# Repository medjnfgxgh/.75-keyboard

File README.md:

# .75-keyboard
An 83 key mechanical keyboard with a rotary encoder for volume and brightness. This was designed to be similar to a 75% keyboard.

### Why?
I was complaining to my friend about how terrible the keyboards in the computer labs at school are, and he suggested I bring my own. One problem, I don't have a spare keyboard. "Just make one", he said, "How hard could it be?". This was very clearly a joke but it did give me an idea for my next project, why not make my very own mechanical keyboard. It would test my CAD and PCB design skills, as well as my soldering, 3d printing and programming knowledge. After a little bit of research, I landed on my design with 83 keys and a rotary encoder.

## The design

## Schematic

## PCB

## Case

# BOM
|           Name           | QTY | Cost | Link |
|--------------------------|-----|------|------|
|Rasberry Pi Pico welded C |  1  |$2.63 |[buy](https://www.aliexpress.com/item/1005005617180169.html)|
|Cherry MX switches        |  9  |$2.33 |[buy](https://www.aliexpress.com/item/1005004341695529.html)|
|Stabilisers               |  1  |$6.82 |[buy](https://www.aliexpress.com/item/1005007041109896.html)|
|Key Caps                  |  1  |$21.62|[buy](https://www.aliexpress.com/item/1005007360831985.html)|
|diodes                    |  1  |$4.48 |[buy](https://www.aliexpress.com/item/1005008994213870.html)|
|EC11                      |  1  |$2.27 |[buy](https://www.aliexpress.com/item/1005007644083514.html)|
|Brass inserts             |  1  |$4.56 |[buy](https://www.aliexpress.com/item/1005006071488810.html)|
|Screws                    |  1  |$6.38 |[buy](https://www.aliexpress.com/item/1005006674812661.html)|
|Female Headers            |  1  |$3.34 |[buy](https://www.aliexpress.com/item/4001198421663.html)|
|subtotal                  |  1  |$73.07|
|Discounts                 |  1  |$-11.5|
|shipping                  |  1  |$7.39
|--------------------------|-----|------|-----|
|AliExpress total          |  1  |$68.96|
|PCB                       |  1  |$35.32|
|--------------------------|-----|------|-----|
|TOTAL                     |  1  |$104.28|

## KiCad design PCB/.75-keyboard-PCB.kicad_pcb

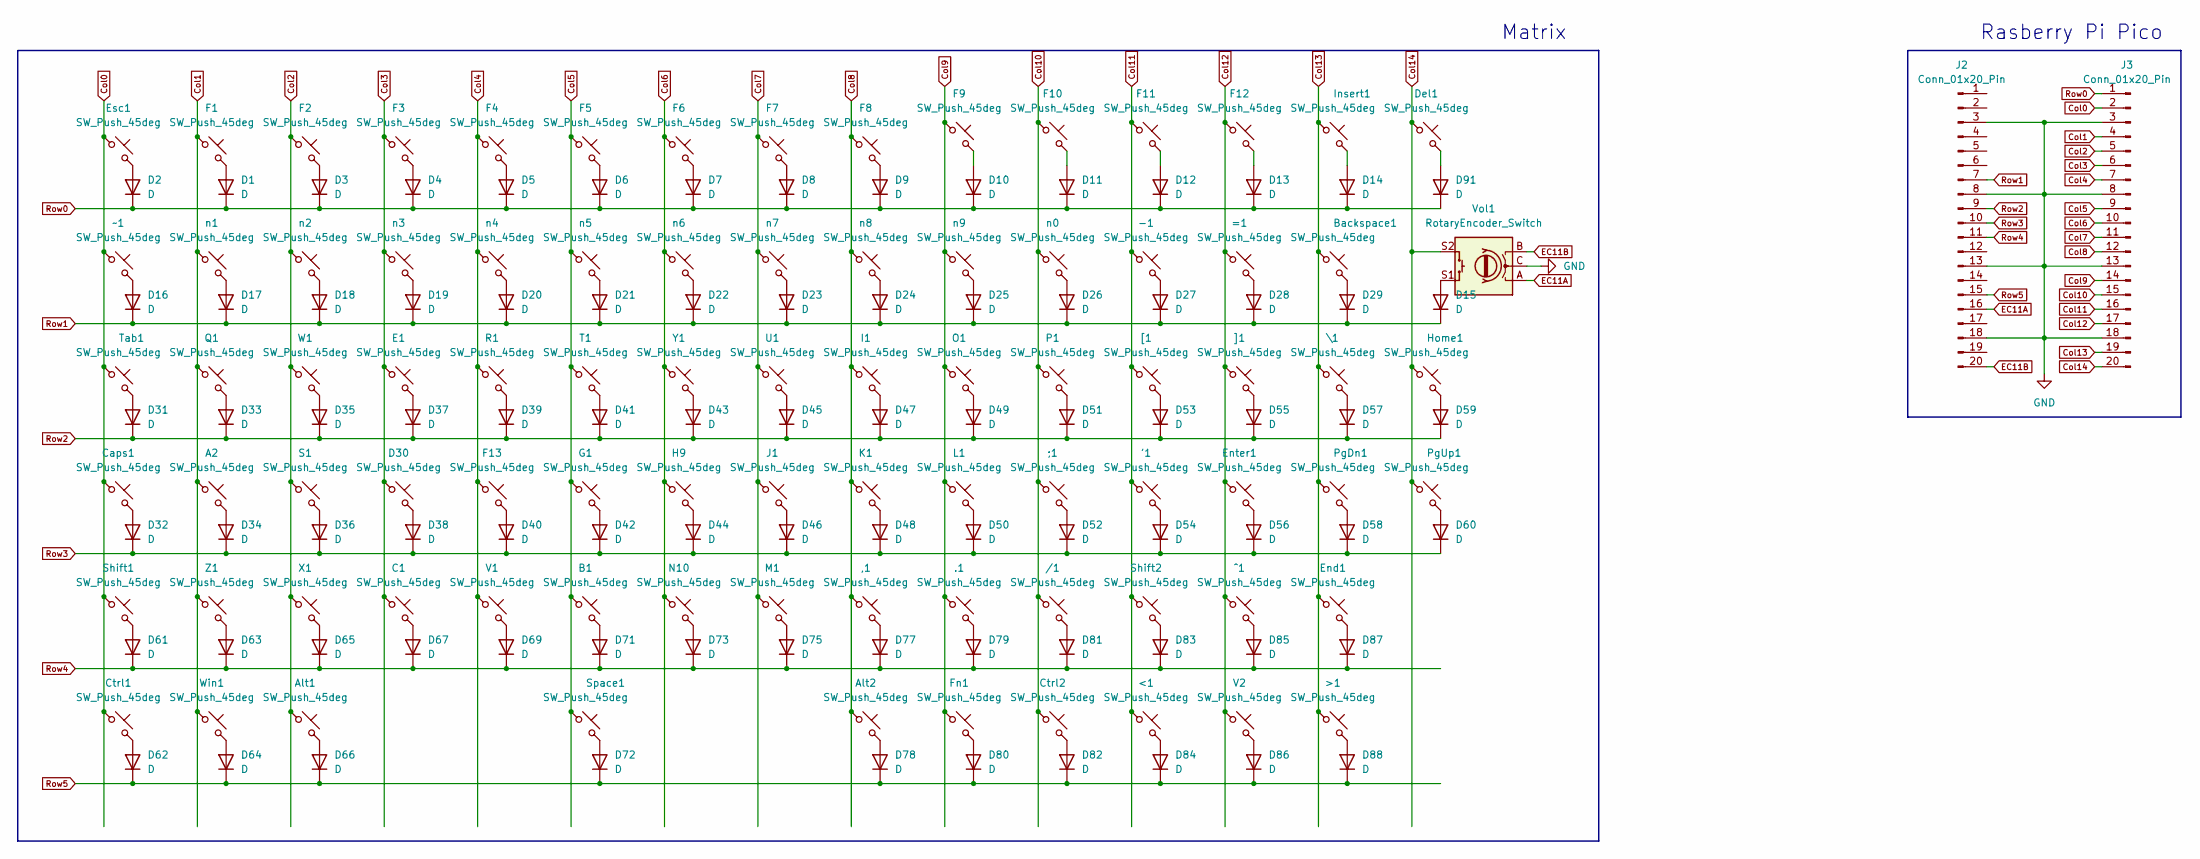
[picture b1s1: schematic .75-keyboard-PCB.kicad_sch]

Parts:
'1: SW_Push_45deg; 3DSW_Cherry_MX_1.00u_PCB
,1: SW_Push_45deg; 3DSW_Cherry_MX_1.00u_PCB
-1: SW_Push_45deg; 3DSW_Cherry_MX_1.00u_PCB
.1: SW_Push_45deg; 3DSW_Cherry_MX_1.00u_PCB
/1: SW_Push_45deg; 3DSW_Cherry_MX_1.00u_PCB
;1: SW_Push_45deg; 3DSW_Cherry_MX_1.00u_PCB
<1: SW_Push_45deg; 3DSW_Cherry_MX_1.00u_PCB
=1: SW_Push_45deg; 3DSW_Cherry_MX_1.00u_PCB
>1: SW_Push_45deg; 3DSW_Cherry_MX_1.00u_PCB
A2: SW_Push_45deg; 3DSW_Cherry_MX_1.00u_PCB
Alt1: SW_Push_45deg; 3DSW_Cherry_MX_1.25u_PCB
Alt2: SW_Push_45deg; 3DSW_Cherry_MX_1.00u_PCB
B1: SW_Push_45deg; 3DSW_Cherry_MX_1.00u_PCB
Backspace1: SW_Push_45deg; 3DSW_Cherry_MX_2.00u_PCB
C1: SW_Push_45deg; 3DSW_Cherry_MX_1.00u_PCB
Caps1: SW_Push_45deg; 3D_SW_Cherry_MX_1.75u_PCB
Ctrl1: SW_Push_45deg; 3DSW_Cherry_MX_1.25u_PCB
Ctrl2: SW_Push_45deg; 3DSW_Cherry_MX_1.00u_PCB
D1, D2, D3, D4, D5, D6, D7, D8, D9, D10, D11, D12, D13, D14, D15, D16, D17, D18, D19, D20, D21, D22, D23, D24, D25, D26, D27, D28, D29, D31, D32, D33, D34, D35, D36, D37, D38, D39, D40, D41, D42, D43, D44, D45, D46, D47, D48, D49, D50, D51, D52, D53, D54, D55, D56, D57, D58, D59, D60, D61, D62, D63, D64, D65, D66, D67, D69, D71, D72, D73, D75, D77, D78, D79, D80, D81, D82, D83, D84, D85, D86, D87, D88, D91: D; D_DO-35_SOD27_P7.62mm_Horizontal
D30: SW_Push_45deg; 3DSW_Cherry_MX_1.00u_PCB
Del1: SW_Push_45deg; 3DSW_Cherry_MX_1.00u_PCB
E1: SW_Push_45deg; 3DSW_Cherry_MX_1.00u_PCB
End1: SW_Push_45deg; 3DSW_Cherry_MX_1.00u_PCB
Enter1: SW_Push_45deg; 3DSW_Cherry_MX_2.25u_PCB
Esc1: SW_Push_45deg; 3DSW_Cherry_MX_1.00u_PCB
F1, F2, F3, F4, F5, F6, F7, F8, F9, F10, F11, F12, F13: SW_Push_45deg; 3DSW_Cherry_MX_1.00u_PCB
Fn1: SW_Push_45deg; 3DSW_Cherry_MX_1.00u_PCB
G1: SW_Push_45deg; 3DSW_Cherry_MX_1.00u_PCB
H9: SW_Push_45deg; 3DSW_Cherry_MX_1.00u_PCB
Home1: SW_Push_45deg; 3DSW_Cherry_MX_1.00u_PCB
I1: SW_Push_45deg; 3DSW_Cherry_MX_1.00u_PCB
Insert1: SW_Push_45deg; 3DSW_Cherry_MX_1.00u_PCB
J1: SW_Push_45deg; 3DSW_Cherry_MX_1.00u_PCB
J2, J3: Conn_01x20_Pin; PinSocket_1x20_P2.54mm_Vertical
K1: SW_Push_45deg; 3DSW_Cherry_MX_1.00u_PCB
L1: SW_Push_45deg; 3DSW_Cherry_MX_1.00u_PCB
M1: SW_Push_45deg; 3DSW_Cherry_MX_1.00u_PCB
N10: SW_Push_45deg; 3DSW_Cherry_MX_1.00u_PCB
O1: SW_Push_45deg; 3DSW_Cherry_MX_1.00u_PCB
P1: SW_Push_45deg; 3DSW_Cherry_MX_1.00u_PCB
PgDn1: SW_Push_45deg; 3DSW_Cherry_MX_1.00u_PCB
PgUp1: SW_Push_45deg; 3DSW_Cherry_MX_1.00u_PCB
Q1: SW_Push_45deg; 3DSW_Cherry_MX_1.00u_PCB
R1: SW_Push_45deg; 3DSW_Cherry_MX_1.00u_PCB
S1: SW_Push_45deg; 3DSW_Cherry_MX_1.00u_PCB
Shift1: SW_Push_45deg; 3DSW_Cherry_MX_2.25u_PCB
Shift2: SW_Push_45deg; 3D_SW_Cherry_MX_1.75u_PCB
Space1: SW_Push_45deg; 3DSW_Cherry_MX_6.25u_PCB
T1: SW_Push_45deg; 3DSW_Cherry_MX_1.00u_PCB
Tab1: SW_Push_45deg; 3DSW_Cherry_MX_1.50u_PCB
U1: SW_Push_45deg; 3DSW_Cherry_MX_1.00u_PCB
V1, V2: SW_Push_45deg; 3DSW_Cherry_MX_1.00u_PCB
Vol1: RotaryEncoder_Switch; RotaryEncoder_Alps_EC11E-Switch_Vertical_H20mm
W1: SW_Push_45deg; 3DSW_Cherry_MX_1.00u_PCB
Win1: SW_Push_45deg; 3DSW_Cherry_MX_1.25u_PCB
X1: SW_Push_45deg; 3DSW_Cherry_MX_1.00u_PCB
Y1: SW_Push_45deg; 3DSW_Cherry_MX_1.00u_PCB
Z1: SW_Push_45deg; 3DSW_Cherry_MX_1.00u_PCB
[1: SW_Push_45deg; 3DSW_Cherry_MX_1.00u_PCB
\1: SW_Push_45deg; 3DSW_Cherry_MX_1.50u_PCB
]1: SW_Push_45deg; 3DSW_Cherry_MX_1.00u_PCB
^1: SW_Push_45deg; 3DSW_Cherry_MX_1.00u_PCB
n0, n1, n2, n3, n4, n5, n6, n7, n8, n9: SW_Push_45deg; 3DSW_Cherry_MX_1.00u_PCB
~1: SW_Push_45deg; 3DSW_Cherry_MX_1.00u_PCB

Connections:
Col0: Caps1.1, Ctrl1.1, Esc1.1, J3.2, Shift1.1, Tab1.1, ~1.1
Col1: A2.1, F1.1, J3.4, Q1.1, Win1.1, Z1.1, n1.1
Col2: Alt1.1, F2.1, J3.5, S1.1, W1.1, X1.1, n2.1
Col3: C1.1, D30.1, E1.1, F3.1, J3.6, n3.1
Col4: F4.1, F13.1, J3.7, R1.1, V1.1, n4.1
Col5: B1.1, F5.1, G1.1, J3.9, Space1.1, T1.1, n5.1
Col6: F6.1, H9.1, J3.10, N10.1, Y1.1, n6.1
Col7: F7.1, J1.1, J3.11, M1.1, U1.1, n7.1
Col8: ,1.1, Alt2.1, F8.1, I1.1, J3.12, K1.1, n8.1
Col9: .1.1, F9.1, Fn1.1, J3.14, L1.1, O1.1, n9.1
Col10: /1.1, ;1.1, Ctrl2.1, F10.1, J3.15, P1.1, n0.1
Col11: '1.1, -1.1, <1.1, F11.1, J3.16, Shift2.1, [1.1
Col12: =1.1, Enter1.1, F12.1, J3.17, V2.1, ]1.1, ^1.1
Col13: >1.1, Backspace1.1, End1.1, Insert1.1, J3.19, PgDn1.1, \1.1
Col14: Del1.1, Home1.1, J3.20, PgUp1.1, Vol1.S2
EC11A: J2.16, Vol1.A
EC11B: J2.20, Vol1.B
GND: J2.3, J2.8, J2.13, J2.18, J3.3, J3.8, J3.13, J3.18, Vol1.C
unnamed: D1.2 (A), F1.2
unnamed: D2.2 (A), Esc1.2
unnamed: D3.2 (A), F2.2
unnamed: D4.2 (A), F3.2
unnamed: D5.2 (A), F4.2
unnamed: D6.2 (A), F5.2
unnamed: D7.2 (A), F6.2
unnamed: D8.2 (A), F7.2
unnamed: D9.2 (A), F8.2
unnamed: D10.2 (A), F9.2
unnamed: D11.2 (A), F10.2
unnamed: D12.2 (A), F11.2
unnamed: D13.2 (A), F12.2
unnamed: D14.2 (A), Insert1.2
unnamed: D15.2 (A), Vol1.S1
unnamed: D16.2 (A), ~1.2
unnamed: D17.2 (A), n1.2
unnamed: D18.2 (A), n2.2
unnamed: D19.2 (A), n3.2
unnamed: D20.2 (A), n4.2
unnamed: D21.2 (A), n5.2
unnamed: D22.2 (A), n6.2
unnamed: D23.2 (A), n7.2
unnamed: D24.2 (A), n8.2
unnamed: D25.2 (A), n9.2
unnamed: D26.2 (A), n0.2
unnamed: -1.2, D27.2 (A)
unnamed: =1.2, D28.2 (A)
unnamed: Backspace1.2, D29.2 (A)
unnamed: D31.2 (A), Tab1.2
unnamed: Caps1.2, D32.2 (A)
unnamed: D33.2 (A), Q1.2
unnamed: A2.2, D34.2 (A)
unnamed: D35.2 (A), W1.2
unnamed: D36.2 (A), S1.2
unnamed: D37.2 (A), E1.2
unnamed: D30.2, D38.2 (A)
unnamed: D39.2 (A), R1.2
unnamed: D40.2 (A), F13.2
unnamed: D41.2 (A), T1.2
unnamed: D42.2 (A), G1.2
unnamed: D43.2 (A), Y1.2
unnamed: D44.2 (A), H9.2
unnamed: D45.2 (A), U1.2
unnamed: D46.2 (A), J1.2
unnamed: D47.2 (A), I1.2
unnamed: D48.2 (A), K1.2
unnamed: D49.2 (A), O1.2
unnamed: D50.2 (A), L1.2
unnamed: D51.2 (A), P1.2
unnamed: ;1.2, D52.2 (A)
unnamed: D53.2 (A), [1.2
unnamed: '1.2, D54.2 (A)
unnamed: D55.2 (A), ]1.2
unnamed: D56.2 (A), Enter1.2
unnamed: D57.2 (A), \1.2
unnamed: D58.2 (A), PgDn1.2
unnamed: D59.2 (A), Home1.2
unnamed: D60.2 (A), PgUp1.2
unnamed: D61.2 (A), Shift1.2
unnamed: Ctrl1.2, D62.2 (A)
unnamed: D63.2 (A), Z1.2
unnamed: D64.2 (A), Win1.2
unnamed: D65.2 (A), X1.2
unnamed: Alt1.2, D66.2 (A)
unnamed: C1.2, D67.2 (A)
unnamed: D69.2 (A), V1.2
unnamed: B1.2, D71.2 (A)
unnamed: D72.2 (A), Space1.2
unnamed: D73.2 (A), N10.2
unnamed: D75.2 (A), M1.2
unnamed: ,1.2, D77.2 (A)
unnamed: Alt2.2, D78.2 (A)
unnamed: .1.2, D79.2 (A)
unnamed: D80.2 (A), Fn1.2
unnamed: /1.2, D81.2 (A)
unnamed: Ctrl2.2, D82.2 (A)
unnamed: D83.2 (A), Shift2.2
unnamed: <1.2, D84.2 (A)
unnamed: D85.2 (A), ^1.2
unnamed: D86.2 (A), V2.2
unnamed: D87.2 (A), End1.2
unnamed: >1.2, D88.2 (A)
unnamed: D91.2 (A), Del1.2
Row0: D1.1 (K), D2.1 (K), D3.1 (K), D4.1 (K), D5.1 (K), D6.1 (K), D7.1 (K), D8.1 (K), D9.1 (K), D10.1 (K), D11.1 (K), D12.1 (K), D13.1 (K), D14.1 (K), D91.1 (K), J3.1
Row1: D15.1 (K), D16.1 (K), D17.1 (K), D18.1 (K), D19.1 (K), D20.1 (K), D21.1 (K), D22.1 (K), D23.1 (K), D24.1 (K), D25.1 (K), D26.1 (K), D27.1 (K), D28.1 (K), D29.1 (K), J2.7
Row2: D31.1 (K), D33.1 (K), D35.1 (K), D37.1 (K), D39.1 (K), D41.1 (K), D43.1 (K), D45.1 (K), D47.1 (K), D49.1 (K), D51.1 (K), D53.1 (K), D55.1 (K), D57.1 (K), D59.1 (K), J2.9
Row3: D32.1 (K), D34.1 (K), D36.1 (K), D38.1 (K), D40.1 (K), D42.1 (K), D44.1 (K), D46.1 (K), D48.1 (K), D50.1 (K), D52.1 (K), D54.1 (K), D56.1 (K), D58.1 (K), D60.1 (K), J2.10
Row4: D61.1 (K), D63.1 (K), D65.1 (K), D67.1 (K), D69.1 (K), D71.1 (K), D73.1 (K), D75.1 (K), D77.1 (K), D79.1 (K), D81.1 (K), D83.1 (K), D85.1 (K), D87.1 (K), J2.11
Row5: D62.1 (K), D64.1 (K), D66.1 (K), D72.1 (K), D78.1 (K), D80.1 (K), D82.1 (K), D84.1 (K), D86.1 (K), D88.1 (K), J2.15

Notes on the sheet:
Matrix
Rasberry Pi Pico

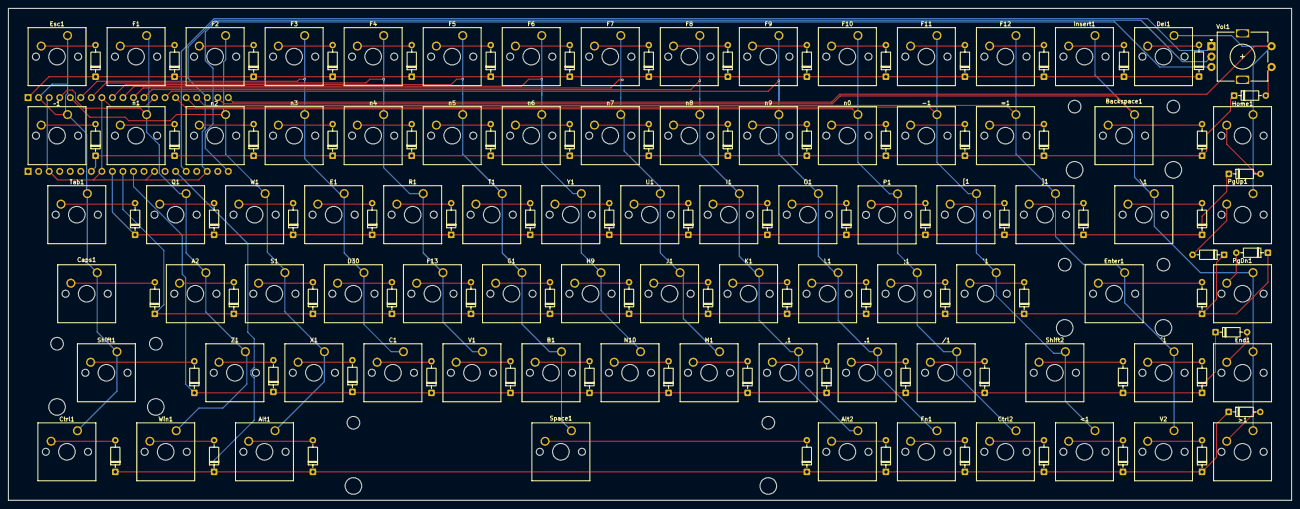
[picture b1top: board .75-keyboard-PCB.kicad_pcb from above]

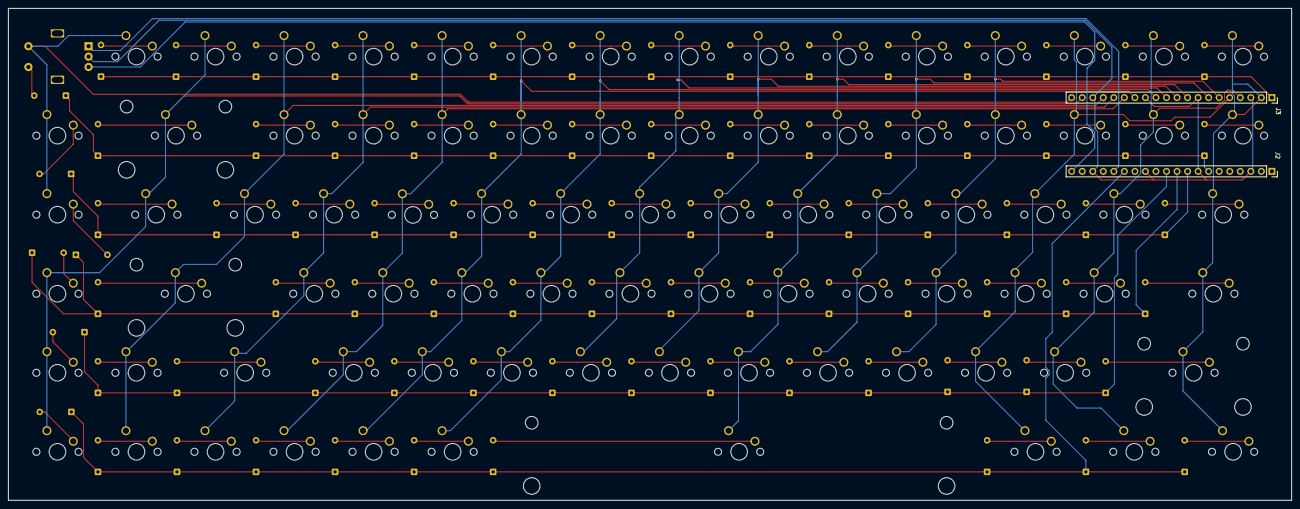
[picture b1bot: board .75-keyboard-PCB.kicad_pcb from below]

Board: 2 copper layers, 309.3 x 118.6 mm, 169 parts (2 on the bottom side), 107 nets.

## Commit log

2026-02-21 Keyboard layout
2026-02-22 Schematic and mostly routed pcb
2026-03-05 pcb routing finished
2026-03-05 kicad switch models
2026-03-05 fix warnings
    repositioned labels to fix warnings
2026-03-31 pcb step
2026-03-31 upload STEP files
2026-03-31 firmware
2026-03-31 gerber
